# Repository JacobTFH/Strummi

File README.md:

# Strummi

## About

The _Strummi_ is a guitar-based Accessible Digital Musical Instrument (ADMI) designed to make guitar playing more physically accessible while preserving the tactile and acoustic response of real guitar strings.
It was developed as part of my PhD research at Queen Mary University of London, with my co-researcher Robert Jack.

The Strummi runs on c++ on the [Bela](https://bela.io/) environment.

You can see videos of the Strummi and find out more about it's use on the [projects](https://jacobtfh.github.io/projects) page of [my website](https://jacobtfh.github.io)

## To do

- Add source code and design files to git repo
- Design GUI in p5.js for changing tunings and chord voicings
- Make Instructables for DMLab AMIC
- Test with cycfi nu pickups
- Improvements to sound: body resonance / pickup modelling etc.

## License

<br />This work is licensed under a <a rel="license" href="http://creativecommons.org/licenses/by-nc/3.0/">Creative Commons Attribution-NonCommercial 3.0 Unported License</a>.

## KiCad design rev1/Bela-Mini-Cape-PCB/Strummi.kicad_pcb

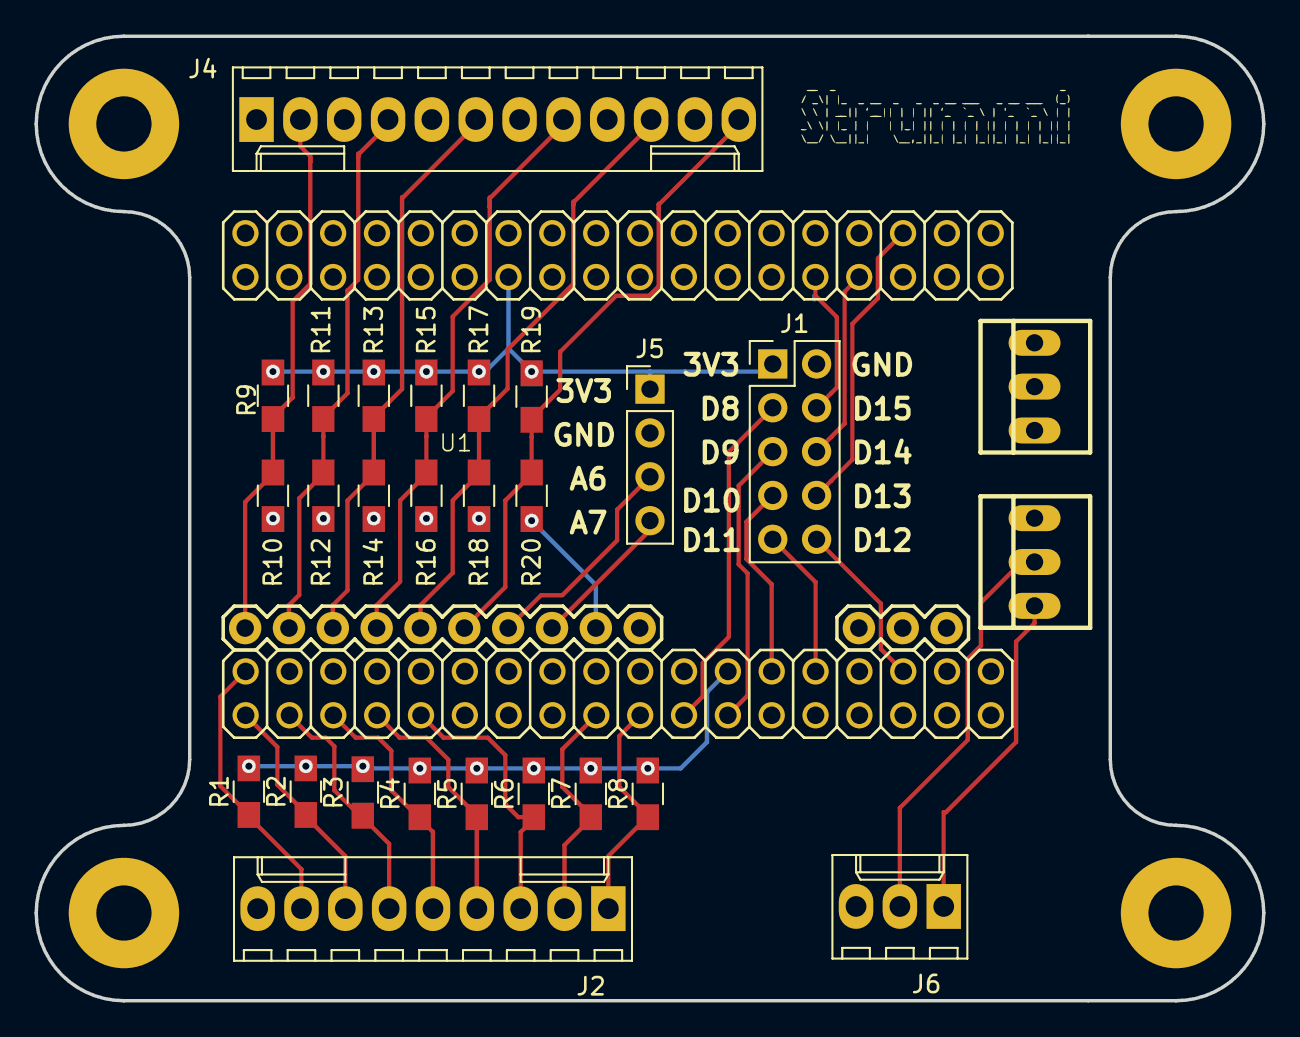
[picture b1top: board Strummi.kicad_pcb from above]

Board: 2 copper layers, 71.1 x 55.9 mm, 26 parts (0 on the bottom side), 28 nets.

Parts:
J1: Conn_01x10_Female; Pin_Header_Straight_2x05_Pitch2.54mm
J2: Conn_01x09_Female; Molex_KK-6410-09_09x2.54mm_Straight
J4: Conn_01x12_Female; Molex_KK-6410-12_12x2.54mm_Straight
J5: Conn_01x04_Female; Pin_Header_Straight_1x04_Pitch2.54mm
J6: Conn_01x03_Female; Molex_KK-6410-03_03x2.54mm_Straight
R1, R2, R3, R4, R5, R6, R7, R8, R9, R10, R11, R12, R13, R14, R15, R16, R17, R18, R19, R20: R; R_0805_HandSoldering
U1: BelaMini_headers; BelaMini_headers_reverse

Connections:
+3V3: J1.1, J5.1, R1.2, R2.2, R3.2, R4.2, R5.2, R6.2, R7.2, R8.2, R9.2, R11.2, R13.2, R15.2, R17.2, R19.2, U1.P1_14, U1.P2_23
/A6: J5.3, U1.A6
/A7: J5.4, U1.A7
/Button0: J2.8, R1.1, U1.P2_01
/Button1: J2.7, R2.1, U1.P2_02
/Button2: J2.6, R3.1, U1.P2_04
/Button3: J2.5, R4.1, U1.P2_06
/Button4: J2.4, R5.1, U1.P2_08
/Button5: J2.3, R6.1, U1.P2_10
/Button6: J2.2, R7.1, U1.P2_18
/Button7: J2.1, R8.1, U1.P2_20
/D8: J1.3, U1.P2_22
/D9: J1.5, U1.P2_24
/D10: J1.7, U1.P2_25
/D11: J1.9, U1.P2_27
/D12: J1.10, U1.P2_31
/D13: J1.8, U1.P1_31
/D14: J1.6, U1.P1_30
/D15: J1.4, U1.P1_28
/Piezo0_B: J4.2, R9.1, R10.1, U1.A0
/Piezo1_B: J4.4, R11.1, R12.1, U1.A1
/Piezo2_B: J4.6, R13.1, R14.1, U1.A2
/Piezo3_B: J4.8, R15.1, R16.1, U1.A3
/Piezo4_B: J4.10, R17.1, R18.1, U1.A4
/Piezo5_B: J4.12, R19.1, R20.1, U1.A5
GNDA: J1.2, J2.9, J4.1, J4.3, J4.5, J4.7, J4.9, J4.11, J5.2, R10.2, R12.2, R14.2, R16.2, R18.2, R20.2, U1.A_GND
unnamed: J6.1, U1.Audio_Out_R
unnamed: J6.2, U1.Audio_Out_L

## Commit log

2020-07-30 Added code and license information
2020-07-30 Fixed license info?
2020-07-30 - Updated readme - Added design files for laser cut enclosure
2020-10-21 Added kicad files for bela mini cape custom PCB
2020-10-28 Changed folder structure.
2020-11-12 Added gerbers.
2020-11-16 Added drill file and zip of gerbers.
2020-11-18 updated with most recent enclosure design files
2020-11-18 Added design files for button PCB support and connections panel
2020-11-25 Added design files for pickup ('piezo sandwich')
2020-11-30 Create BoM.md
    updating bill of materials
